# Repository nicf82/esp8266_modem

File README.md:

Virtual modem for ESP8266
=========================

Schematic Copyright (C) 2018 Daniel Jameson <djameson@gmail.com>
PCB Copyright (C) 2018 Daniel Jameson <djameson@gmail.com>
Schematic and PCB released under Creative Commons Attribution-ShareAlike 4.0 License: https://creativecommons.org/licenses/by-sa/4.0/legalcode

FreeFi232 is UNTESTED!

Firmware Copyright (C) 2015 Jussi Salin <salinjus@gmail.com> under GPLv3 license.
Additions Copyright (C) 2018 Daniel Jameson <djameson@gmail.com> and Stardot contributers under GPLv3 license.

Getting Started with the BBC Micro
----------------------------------
You will need:
1x LoLin NodeMCU board with an ESP12E module on it 
1x MAX3232 level shifter board - not just the IC on its own! 
1x Domino plug for the beeb's serial...
Some wire for wiring things together.

On your modern computer you need:
The Arduino IDE: https://www.arduino.cc/en/Main/Software
The source for the firmware. If you wish to compile it with hardware flow (RTS/CTS), make sure you've got access to GPIO pins 13/15 of the ESP8266 and adjust the #defines in the source.  Ensure RTS/CTS are hooked up appropriately to your terminal.

On the beeb you need:
Commstar 1.4

1st, you need to get the ESP8266 environment set up on the Arduino IDE. Instructions here: 
http://www.instructables.com/id/Quick-Start-to-Nodemcu-ESP8266-on-Arduino-IDE/

Once you're sure that you can compile and upload sketches to the NodeMCU board, compile and upload the ESP8266 modem sketch. 

Next step is to hook this up to the BBC/Master.

On the domino plug, looking at the solder side, join pins 5/2 (RTS/CTS), and take lines from GND (centre pin 1), RD (4) and TD (3).
Take TD to the TxD pin on your level shifter and RD to the RxD pin, and GND to GND.

On the other side, the MAX3232 will need 3.3V from somewhere and you can bring the GND from it out to attach to the LoLin board... 

Connect the TxD output to the TX pin on the LoLin board, and the RxD output to the RX pin of the LoLin board, GND to G, and then it's up to you to choose how to power the LoLin board - you can take 5V and feed that to the VIN pin, or you can just use a USB adapter and power it through that. Entirely up to you. JUST DON'T FEED 5V TO ONE OF THE PINS MARKED 3V! YOU WILL FRY YOUR BOARD!

You should now have a working WiFi telnet modem!

More General Overview
---------------------

ESP8266 is a tiny MCU module with WIFI. It already contains a virtual modem firmware by factory but I wanted to make one myself to support a wider range of baud rates. For example Commodore 64 requires 2400 or lower. Now it is also possible to add additional features in the future because this is open source. For example, translation tables for different character sets or file transfer protocol conversions on the fly with help of a buffer in MCU memory.

AT command examples
-------------------

* Change baud rate: AT115200
* Connect to WIFI: ATWIFIMyAccessPoint,MyPassword1234
* Connect by TCP: ATDTsome.bbs.com:23
* Disable telnet command handling: ATNET0
* Get my IP: ATIP
* Make a HTTP GET request: ATGEThttp://host:80/path
* Answer a RING: ATA
* Disconnect: +++ (following a delay of a second)

Note that the key and port are optional parameters. Port defaults to 23. All parameters are case sensitive, the command itself not. You must always connect to an access point before dialing, otherwise you get an error. When you connect to WIFI you get either OK or ERROR after a while, depending on if it succeeded. If you get ERROR the connection might still occur by itself some time later, in case you had a slow AP or slow DHCP server in the network. When dialing, you get either CONNECT when successfully connected or ERROR if the connection couldn't be made. Reasons can be that the remote service is down or the host name is mistyped.

Default Baud rate is defined in the code. 2400 is safe for C64 and 19200 for any PC and Amiga. 115200 for PC's with "new" 16550 UART.  You must always have that default rate on the terminal when powering on. After giving a command for a higher rate nothing is replied, just switch to the new baud rate in your terminal as well. Then you can give next command in the new baud rate. Note that the first command after switching baud rate might fail because the serial port hardware is not fully synchronized yet, so it might be good idea to simply give "AT" command and wait for "ERROR" or "OK" before giving an actual command.

Example communication
---------------------

	OK
	ATWIFIMyAccessPoint,MyPassword
	Connecting to MyAccessPoint/MyPassword
	OK
	ATDTbat.org
	Connecting to bat.org:23
	CONNECT

	    __|\/|__             __|\/|__           __|\/|__       __|\/|__  Logo
	     \<..>/               \<..>/             \<..>/         \<..>/    by:
	             |\_/|                                      |\_/|          Gar
	       ______|0 0|______   /////// //\\ \\\\\\\   ______|0 0|______
	        \| | |   |  | |/  //   // //  \\    \\     \| | |   |  | |/
	          \|..\./...|/   /////// ////\\\\    \\      \|..\./...|/

A more detailed example can be seen on my YouTube video at: https://youtu.be/oiP5Clx3D_s

Hints
-----

The module can also be used for other than telnet connections, for example you can connect to HTTP port, send a HTTP request and receive a response.

I made a 3D printable case for the C64: http://www.thingiverse.com/thing:1545605 If you build it for any other device you can use any generic case because you need room for a RS232 level converter such as MAX232, and you do not need holes for any rare connectors.

Future plans and status
-----------------------

* It seems quite complete for me but please send ideas.
* I tested huge transfers with ZModem, seems to be working. Remember to use -e parameter with sz and rz if using over a telnetd.
* Serial multiplayer game of Doom (sersetup.exe) seems to be also working. Remember to use ATNET0 when playing serial games, also on DosBox emulator if it's the other host.

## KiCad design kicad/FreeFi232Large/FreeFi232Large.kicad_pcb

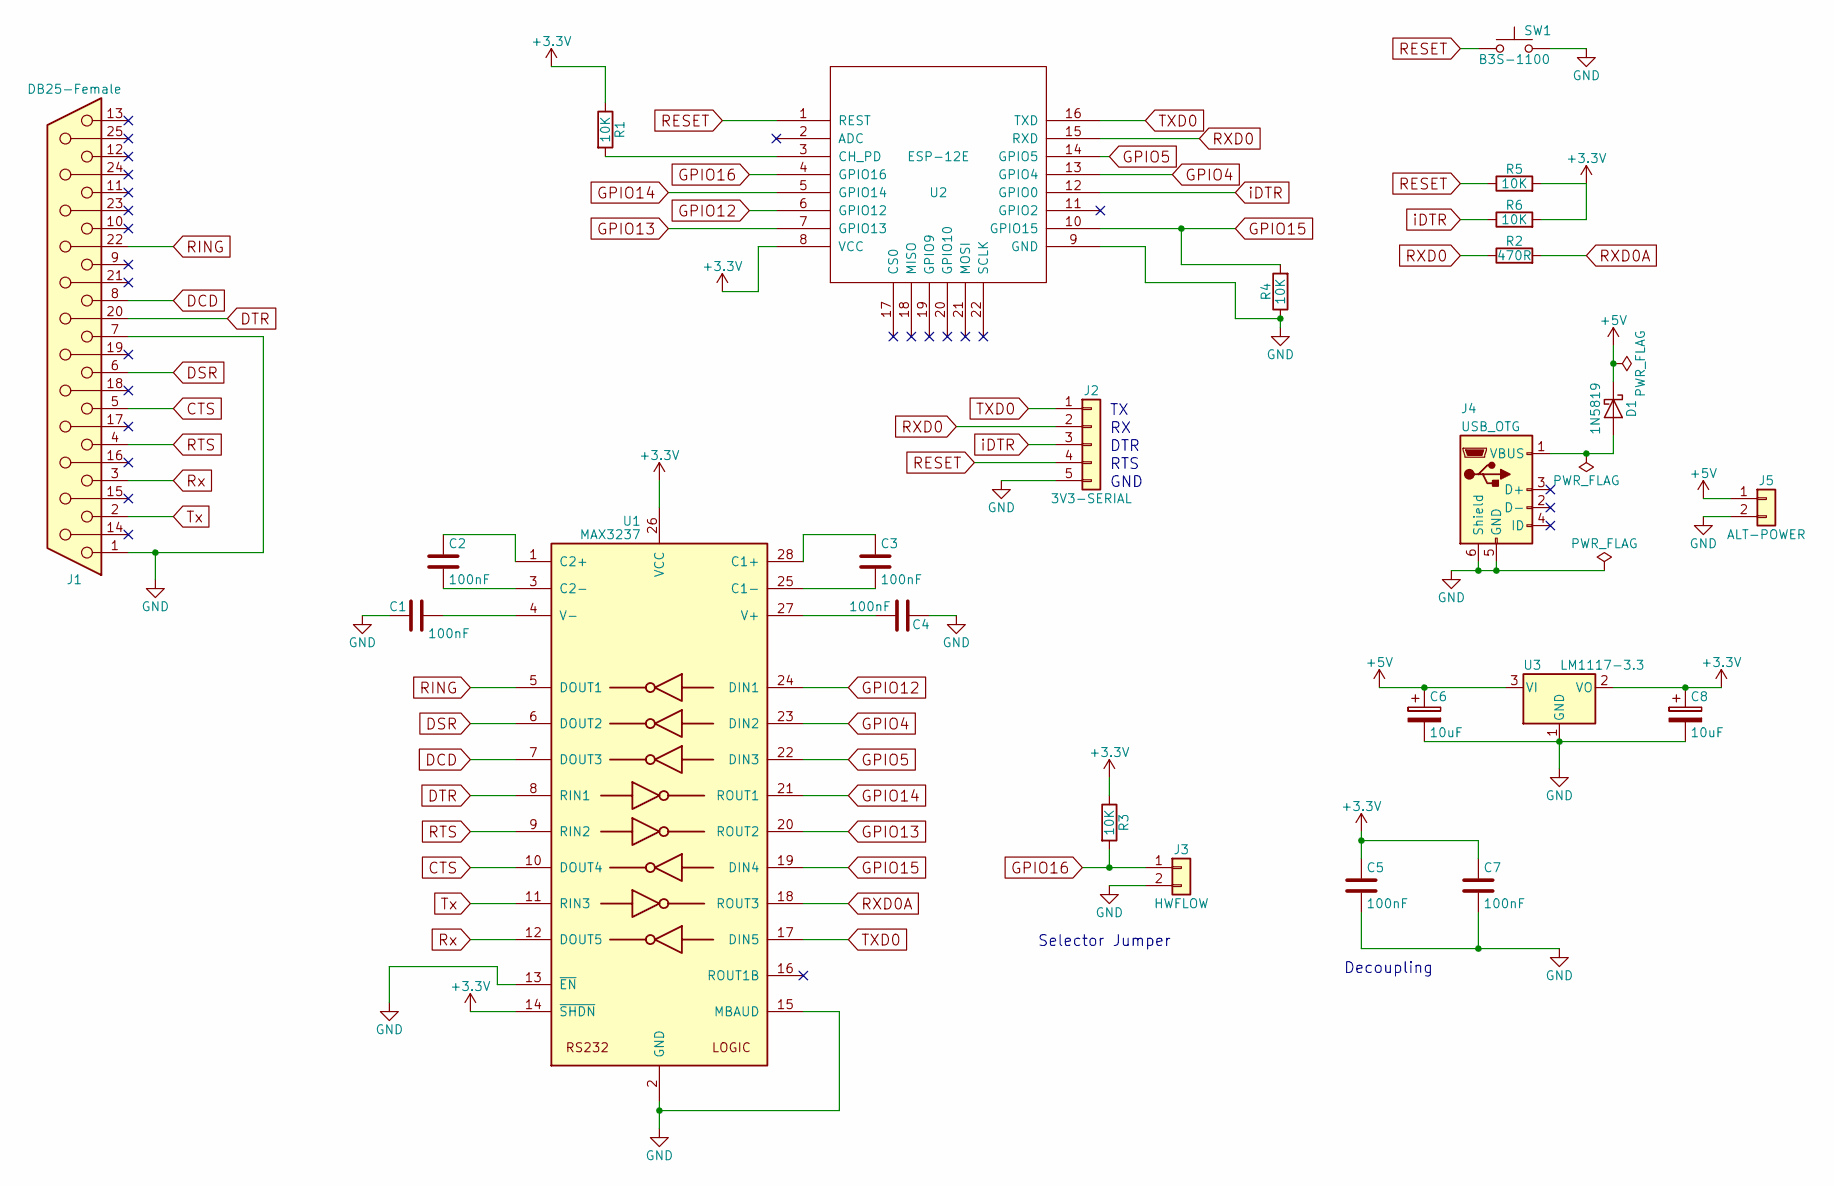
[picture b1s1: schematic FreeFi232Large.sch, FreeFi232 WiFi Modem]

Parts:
C1, C2, C3, C4, C5, C7: 100nF; C_0805
C6, C8: 10uF; CP_Tantalum_Case-B_EIA-3528-21_Reflow
D1: 1N5819; D_SOD-323
J1: DB25-Female; DB25F_CI
J2: 3V3-SERIAL; Pin_Header_Straight_1x05_Pitch2.54mm
J3: HWFLOW; Pin_Header_Straight_1x02_Pitch2.54mm
J4: USB_OTG; USB_Micro-B_Molex-105017-0001
J5: ALT-POWER; Pin_Header_Straight_1x02_Pitch2.54mm
R1, R3, R4, R5, R6: 10K; R_0805
R2: 470R; R_0805
SW1: B3S-1100; Panasonic_EVPAA
U1: MAX3237; SSOP-28_5.3x10.2mm_Pitch0.65mm
U2: ESP-12E; ESP-12E_SMD
U3: LM1117-3.3; SOT-223

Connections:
+3V3: C5.1, C7.1, C8.1, R1.1, R3.1, R5.2, R6.2, U1.14 (~SHDN), U1.26 (VCC), U2.8 (VCC), U3.2 (VO)
+5V: C6.1, D1.1 (K), J5.1, U3.3 (VI)
CTS: J1.5, U1.10 (DOUT4)
DCD: J1.8, U1.7 (DOUT3)
DSR: J1.6, U1.6 (DOUT2)
DTR: J1.20, U1.8 (RIN1)
GND: C1.1, C4.1, C5.2, C6.2, C7.2, C8.2, J1.1, J1.7, J2.5, J3.2, J4.5 (GND), J4.6 (Shield), J5.2, R4.1, SW1.2, U1.2 (GND), U1.13 (~EN), U1.15 (MBAUD), U2.9 (GND), U3.1 (GND)
GPIO4: U1.23 (DIN2), U2.13 (GPIO4)
GPIO5: U1.22 (DIN3), U2.14 (GPIO5)
GPIO12: U1.24 (DIN1), U2.6 (GPIO12)
GPIO13: U1.20 (ROUT2), U2.7 (GPIO13)
GPIO14: U1.21 (ROUT1), U2.5 (GPIO14)
GPIO15: R4.2, U1.19 (DIN4), U2.10 (GPIO15)
GPIO16: J3.1, R3.2, U2.4 (GPIO16)
unnamed: C1.2, U1.4 (V-)
unnamed: C2.1, U1.1 (C2+)
unnamed: C2.2, U1.3 (C2-)
unnamed: C3.1, U1.28 (C1+)
unnamed: C3.2, U1.25 (C1-)
unnamed: C4.2, U1.27 (V+)
unnamed: D1.2 (A), J4.1 (VBUS)
unnamed: R1.2, U2.3 (CH_PD)
RESET: J2.4, R5.1, SW1.1, U2.1 (REST)
RING: J1.22, U1.5 (DOUT1)
RTS: J1.4, U1.9 (RIN2)
RXD0: J2.2, R2.1, U2.15 (RXD)
RXD0A: R2.2, U1.18 (ROUT3)
Rx: J1.3, U1.12 (DOUT5)
TXD0: J2.1, U1.17 (DIN5), U2.16 (TXD)
Tx: J1.2, U1.11 (RIN3)
iDTR: J2.3, R6.1, U2.12 (GPIO0)

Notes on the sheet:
Decoupling
RTS
GND
DTR
Selector Jumper

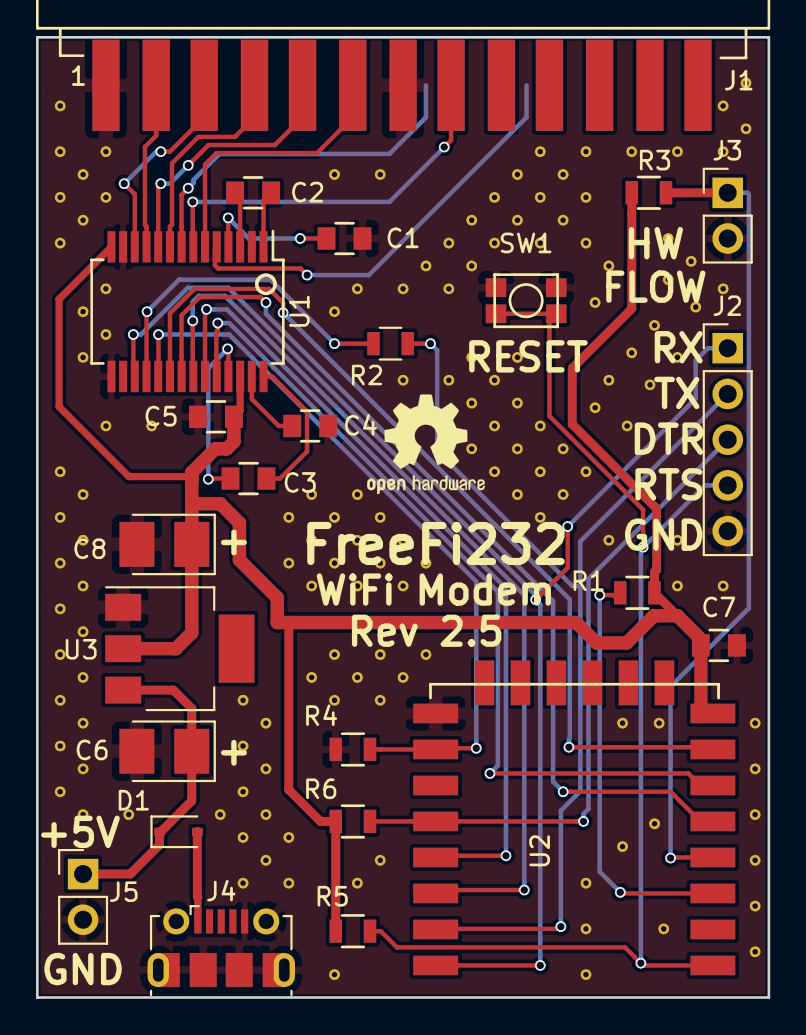
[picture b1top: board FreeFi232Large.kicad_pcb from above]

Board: 2 copper layers, 40.6 x 53.3 mm, 24 parts (0 on the bottom side), 31 nets.

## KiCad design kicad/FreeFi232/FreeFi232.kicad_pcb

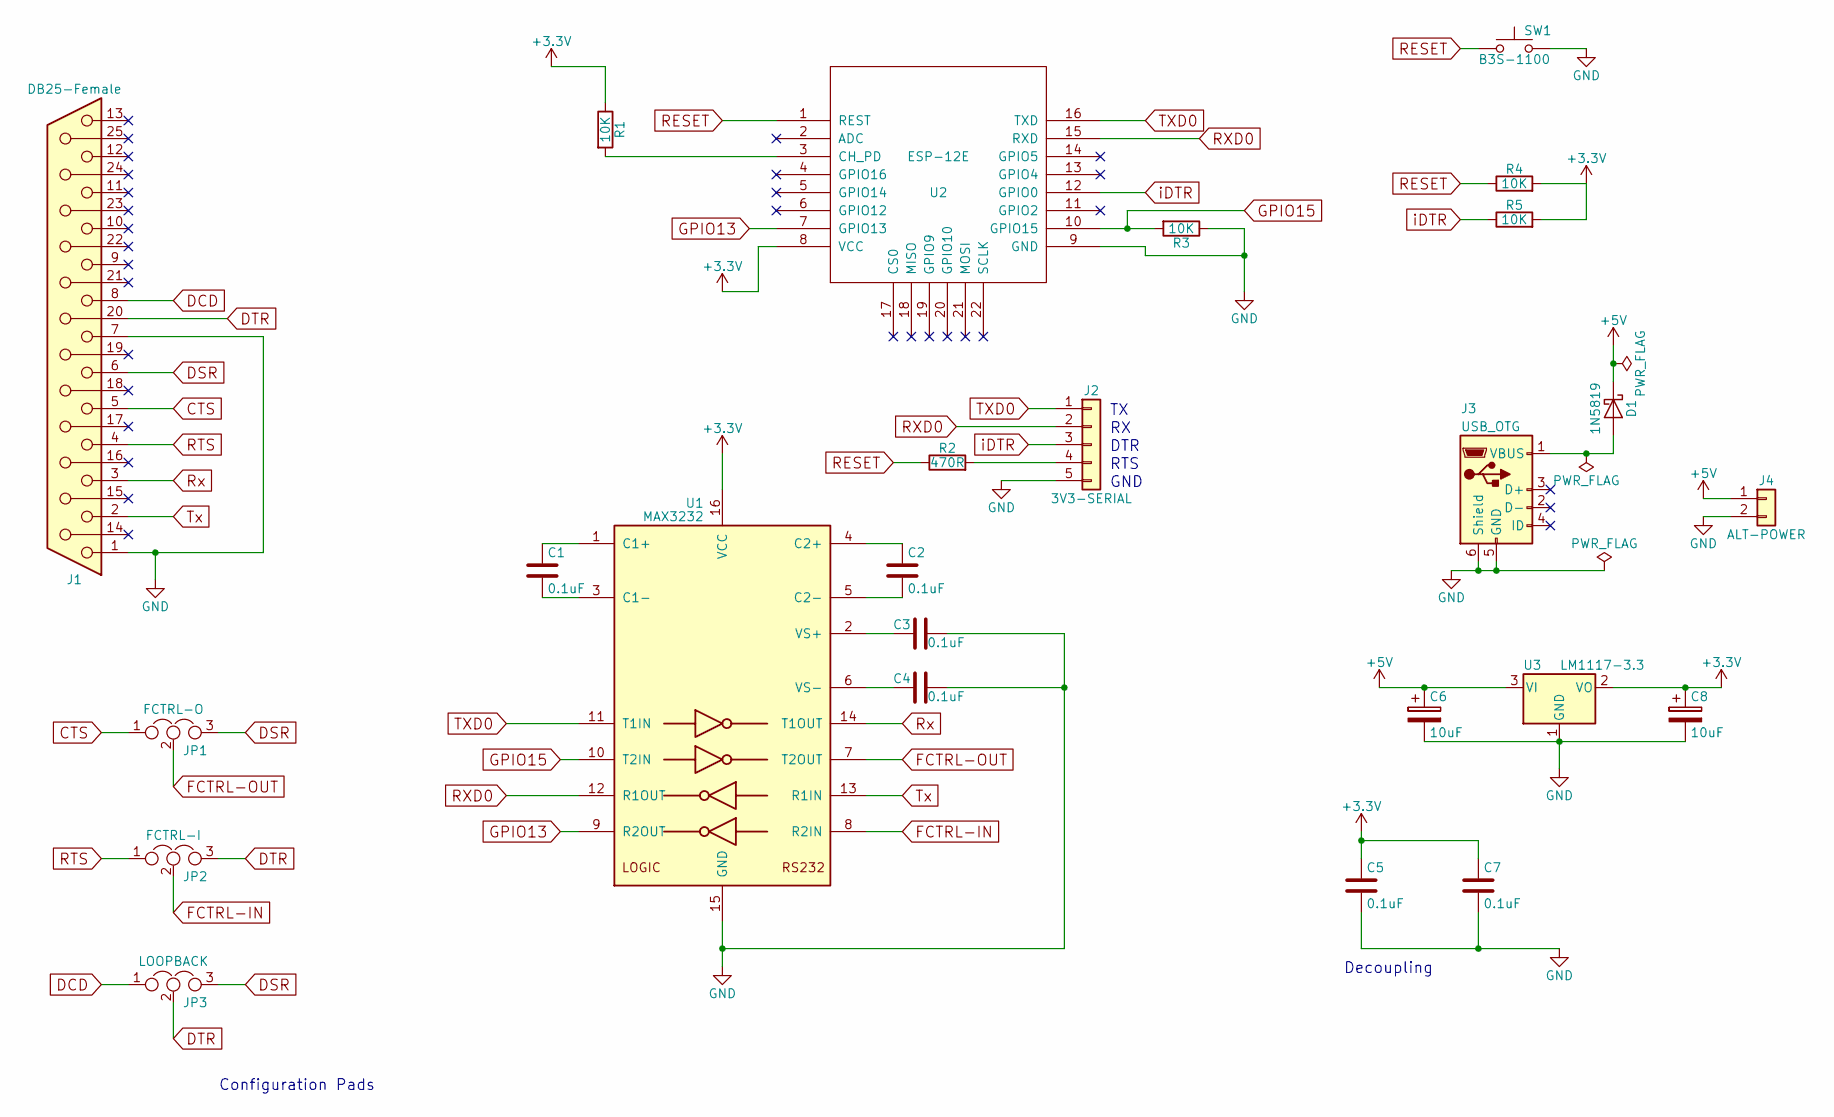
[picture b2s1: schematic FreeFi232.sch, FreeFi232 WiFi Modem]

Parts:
C1, C2, C3, C4, C5, C7: 0.1uF; C_0805
C6, C8: 10uF; CP_Tantalum_Case-B_EIA-3528-21_Reflow
D1: 1N5819; D_SOD-323
J1: DB25-Female; DB25F_CI
J2: 3V3-SERIAL; Pin_Header_Angled_1x05_Pitch2.54mm
J3: USB_OTG; USB_Micro-B
J4: ALT-POWER; Pin_Header_Angled_1x02_Pitch2.54mm
JP1: FCTRL-O; GS3
JP2: FCTRL-I; GS3
JP3: LOOPBACK; GS3
R1, R3, R4, R5: 10K; R_0805
R2: 470R; R_0805
SW1: B3S-1100; Panasonic_EVPAA
U1: MAX3232; SOIC-16
U2: ESP-12E; ESP-12E_SMD
U3: LM1117-3.3; SOT-223

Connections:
+3V3: C5.1, C7.1, C8.1, R1.1, R4.2, R5.2, U1.16 (VCC), U2.8 (VCC), U3.2 (VO)
+5V: C6.1, D1.1 (K), J4.1, U3.3 (VI)
CTS: J1.5, JP1.1
DCD: J1.8, JP3.1
DSR: J1.6, JP1.3, JP3.3
DTR: J1.20, JP2.3, JP3.2
FCTRL-IN: JP2.2, U1.8 (R2IN)
FCTRL-OUT: JP1.2, U1.7 (T2OUT)
GND: C3.2, C4.2, C5.2, C6.2, C7.2, C8.2, J1.1, J1.7, J2.5, J3.5 (GND), J3.6 (Shield), J4.2, R3.1, SW1.2, U1.15 (GND), U2.9 (GND), U3.1 (GND)
GPIO13: U1.9 (R2OUT), U2.7 (GPIO13)
GPIO15: R3.2, U1.10 (T2IN), U2.10 (GPIO15)
unnamed: C1.1, U1.1 (C1+)
unnamed: C1.2, U1.3 (C1-)
unnamed: C2.1, U1.4 (C2+)
unnamed: C2.2, U1.5 (C2-)
unnamed: C3.1, U1.2 (VS+)
unnamed: C4.1, U1.6 (VS-)
unnamed: D1.2 (A), J3.1 (VBUS)
unnamed: J2.4, R2.2
unnamed: R1.2, U2.3 (CH_PD)
RESET: R2.1, R4.1, SW1.1, U2.1 (REST)
RTS: J1.4, JP2.1
RXD0: J2.2, U1.12 (R1OUT), U2.15 (RXD)
Rx: J1.3, U1.14 (T1OUT)
TXD0: J2.1, U1.11 (T1IN), U2.16 (TXD)
Tx: J1.2, U1.13 (R1IN)
iDTR: J2.3, R5.1, U2.12 (GPIO0)

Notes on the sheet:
Decoupling
RTS
GND
DTR
Configuration Pads

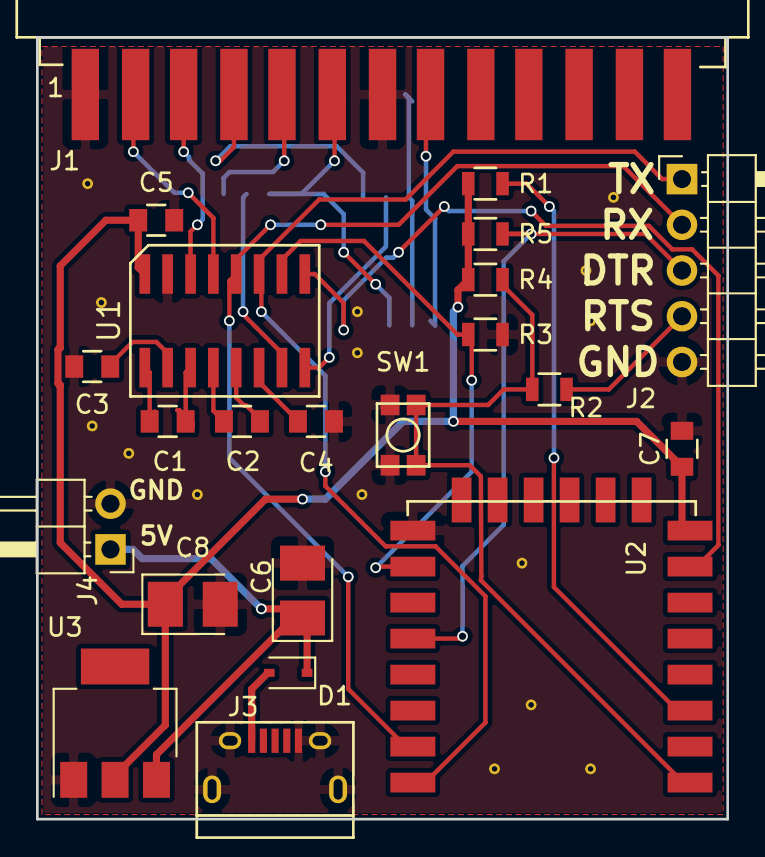
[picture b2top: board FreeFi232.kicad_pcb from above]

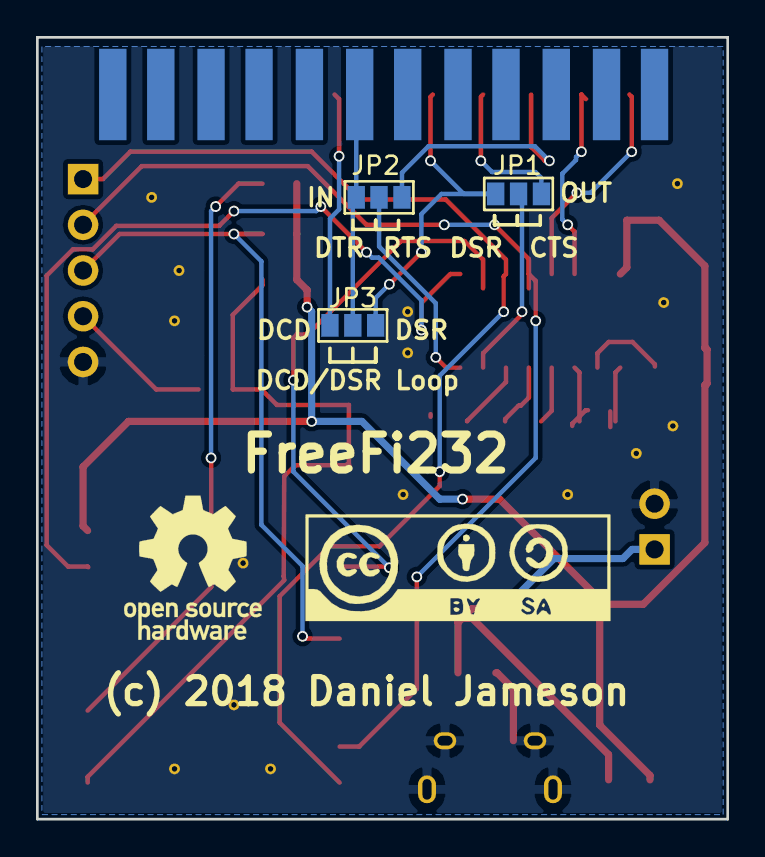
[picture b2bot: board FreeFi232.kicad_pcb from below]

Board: 2 copper layers, 38.4 x 43.4 mm, 25 parts (3 on the bottom side), 27 nets.

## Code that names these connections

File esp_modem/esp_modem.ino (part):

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
//#defines

#define USE_HW_FLOW_CTRL   // Use hardware (RTS/CTS) flow control - controlled by HW_FLOW_SELECT GPIO being pulled LOW.
//#undef USE_HW_FLOW_CTRL      // comment out line above to disable HW flow and uncomment this one.
#ifdef USE_HW_FLOW_CTRL
#include <uart_register.h>
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#undef DEBUG
#define DEFAULT_BPS 2400   // 2400 safe for all old computers including C64
#define LISTEN_PORT 23     // Listen to this if not connected. Set to zero to disable.
#define RING_INTERVAL 3000 // How often to print RING when having a new incoming connection (ms)
#define MAX_CMD_LENGTH 256 // Maximum length for AT command
#define LED_PIN 2          // Status LED
#define LED_TIME 1         // How many ms to keep LED on at activity
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bool telnet = true;        // Is telnet control code handling enabled
bool dacomAutoAnswer = false; // are we looking to auto-answer in dacom mode?

unsigned long lastRingMs = 0; // Time of last "RING" message (millis())
long myBps;                // What is the current BPS setting
char plusCount = 0;        // Go to AT mode at "+++" sequence, that has to be counted
char ctrlACount = 0;       // Go to DaCom command mode with 4xCTRL-A
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#ifdef USE_HW_FLOW_CTRL
void setHardwareFlow() {
  // Enable flow control of DTE -> ESP8266 data with RTS
  // RTS on the EPS8266 is pin GPIO15 which is physical pin 16
  // RTS on the ESP8266 is an output and should be connected to CTS on the RS423
  // The ESP8266 has a 128 byte receive buffer, so a threshold of 64 is half full
  pinMode(ESP_RTS, FUNCTION_4); // make pin U0RTS
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  SET_PERI_REG_MASK(UART_CONF1(0), UART_RX_FLOW_EN);

  // Enable flow control of ESP8266 -> DTE data with CTS
  // CTS on the EPS8266 is pin GPIO13 which is physical pin 7
  // CTS on the ESP8266 is an input and should be connected to RTS on the RS423
  pinMode(ESP_CTS, FUNCTION_4); // make pin U0CTS
  SET_PERI_REG_MASK(UART_CONF0(0), UART_TX_FLOW_EN);
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
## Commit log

2018-05-05 Revert "CTS/RTS flow control in this fork."
2018-05-11 Small delay added to stop ESP8266 crash.
2018-05-11 Updated README.md with specific details for beeb.
2018-05-15 Using a MAX3232, not 232
2018-05-15 Tidying up.
2018-05-16 Add optional for enabling hardware flow control (untested)
2018-05-16 Fixes to hardware flow control, seems to work
2018-05-17 Added KiCad files
2018-05-17 Adding KiCad Files
2018-05-17 update copyrights
2018-05-18 HW Flow off by default, updated README.
2018-05-19 Fix delay, ensure flow control enabled after baud change.
2018-06-10 FreeFi232Large - implements full RS232.
2018-06-10 Finalised Rev 2 of PCB.
2018-06-10 Gerbers added.
2018-06-19 Updates to PCB
2018-06-20 PCB to V1.1
2018-06-20 Final tidying of power lines.
2018-07-04 Reverted to KiCAD 4.0.7, revised GPIO pins, BOM added.
2018-07-05 updated silkscreen
2018-07-06 Updates to software to check new pins.
2018-07-06 Schematic corrections - pullup added on RX programming port, GPIOs adjusted.
2018-07-06 Support for all RS232 pins added to modem software. Flow control hardware selectable.
2018-07-06 Error corrected in schematic and PCB. Gerbers updated.
2018-07-09 Starting to refactor code with aim to add communitel modem compatibility
2018-07-10 Added description of CommunITEL modem commands, split sketch out into multiple files.
2018-07-12 Display MAC address in help message.
2018-07-14 DaCom mode, initial commands implemented. No dialing yet.
2018-07-26 Version 2.5 of PCB/Schematic - current limiting resistor between MAX3237 and ESP12
2018-07-28 Tidied up some power traces.
2018-07-28 removed old 3232 version
2022-12-25 Fix compile error when USE_HW_FLOW_CTRL defined

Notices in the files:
esp_modem/esp_modem.ino:
Original Source Copyright (C) 2016 Jussi Salin <salinjus@gmail.com>
Additions (C) 2018 Daniel Jameson, Stardot Contributors
This program is free software: you can redistribute it and/or modify
it under the terms of the GNU General Public License as published by
the Free Software Foundation, either version 3 of the License, or
(at your option) any later version.
kicad/FreeFi232/FreeFi232.kicad_pcb:
CC-BY-SA 4.0
kicad/FreeFi232/FreeFi232.sch:
License: CC-BY-SA 4.0
